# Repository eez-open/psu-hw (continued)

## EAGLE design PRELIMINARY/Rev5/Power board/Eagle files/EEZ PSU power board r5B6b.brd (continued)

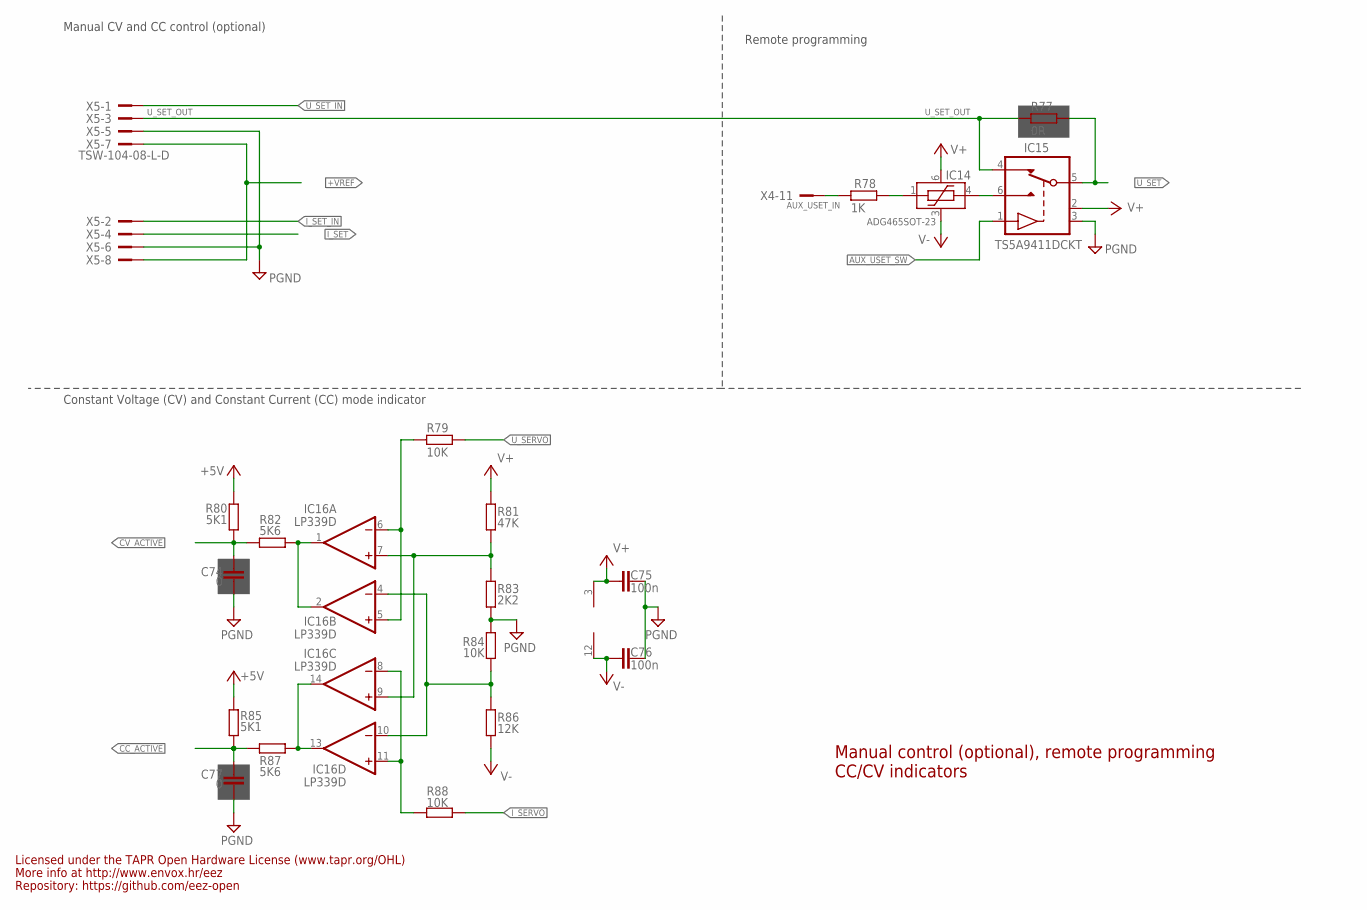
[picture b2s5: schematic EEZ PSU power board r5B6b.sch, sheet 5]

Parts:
C74, C77: 0; C0603
C75, C76: 100n; C0603
IC14: ADG465SOT-23; SOT95P280X145-6N
IC15: TS5A9411DCKT; SOT65P210X110-6N
IC16: LP339D; SOIC127P600X175-14N
R77: 0R; R0805
R78: 1K; R0805
R79, R84, R88: 10K; R0805
R80, R85: 5K1; R0805
R81: 47K; R0805
R82, R87: 5K6; R0805
R83: 2K2; R0805
R86: 12K; R0805
X4: SSW-113-02-T-D-RA; FARNELL 1805583
X5: TSW-104-08-L-D; TSW-104-02-S-D

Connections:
+5V: R80.2, R85.2; also elsewhere on the board
+VREF: X5.7, X5.8; also elsewhere on the board
AUX_USET_IN: R78.2, X4.11
AUX_USET_SW: IC15.1 (IN); also elsewhere on the board
CC_ACTIVE: C77.1, R85.1, R87.2; also elsewhere on the board
CV_ACTIVE: C74.1, R80.1, R82.2; also elsewhere on the board
GND: C74.2, C75.1, C76.1, C77.2, IC15.3 (GND), R83.1, R84.2, X5.5, X5.6; also elsewhere on the board
I_SERVO: R88.1; also elsewhere on the board
I_SET: X5.4; also elsewhere on the board
I_SET_IN: X5.2; also elsewhere on the board
unnamed: IC14.4 (VS), IC15.6 (S1)
unnamed: IC14.1 (VD), R78.1
unnamed: IC16.1 (OUT), IC16.2 (OUT), R82.1
unnamed: IC16.13 (OUT), IC16.14 (OUT), R87.1
unnamed: IC16.5 (+IN), IC16.6 (-IN), R79.2
unnamed: IC16.8 (-IN), IC16.11 (+IN), R88.2
unnamed: IC16.7 (+IN), IC16.9 (+IN), R81.1, R83.2
unnamed: IC16.4 (-IN), IC16.10 (-IN), R84.1, R86.2
U_SERVO: R79.1; also elsewhere on the board
U_SET: IC15.5 (D), R77.1; also elsewhere on the board
U_SET_IN: X5.1; also elsewhere on the board
U_SET_OUT: IC15.4 (S2), R77.2, X5.3
V+: C75.2, IC14.6 (VDD), IC15.2 (VDD), IC16.3 (V+), R81.2; also elsewhere on the board
V-: C76.2, IC14.3 (VSS), IC16.12 (GND), R86.1; also elsewhere on the board

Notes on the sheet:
Constant Voltage (CV) and Constant Current (CC) mode indicator
Manual CV and CC control (optional)
CC/CV indicators
Licensed under the TAPR Open Hardware License (www.tapr.org/OHL)
Repository: https://github.com/eez-open
More info at http://www.envox.hr/eez
Manual control (optional), remote programming
Remote programming

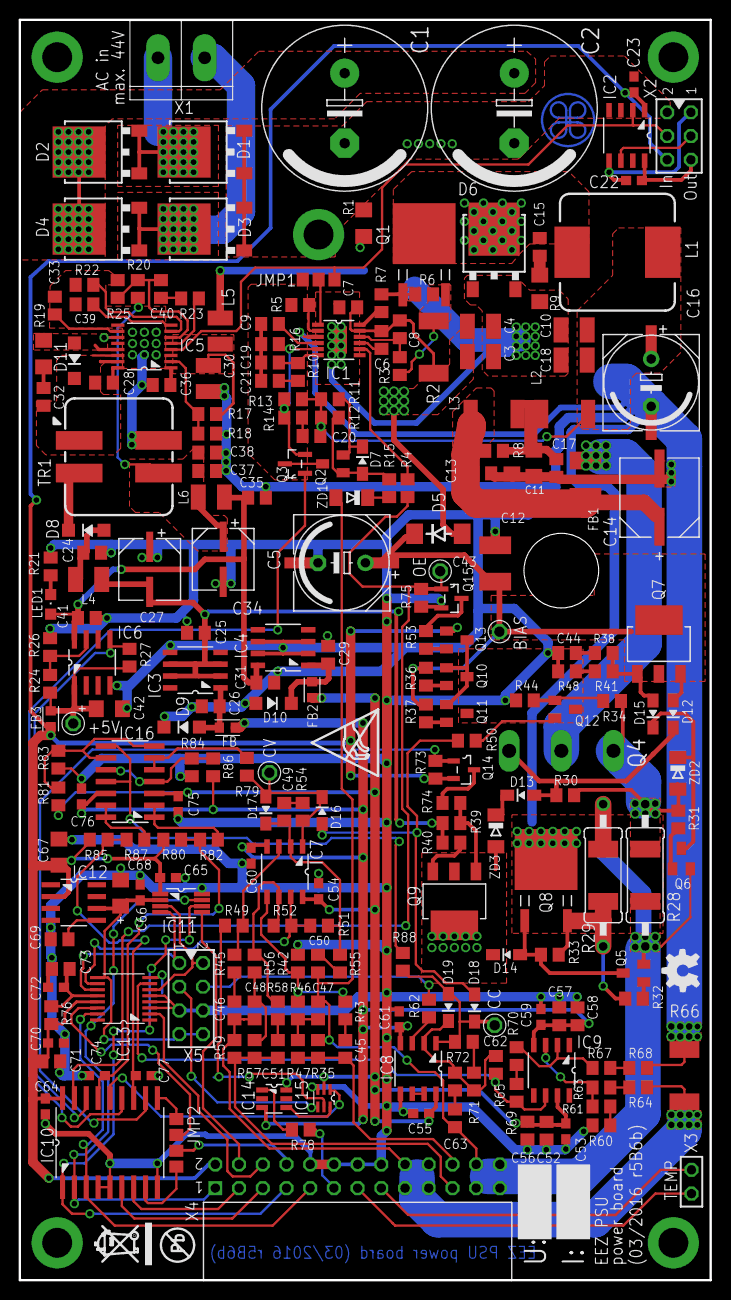
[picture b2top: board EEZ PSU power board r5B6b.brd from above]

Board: 3 copper layers, 74.0 x 135.0 mm, 248 parts (1 on the bottom side), 151 nets.

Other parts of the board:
EEZ_SIGNATURE: SIGNATURESMALL; SIGNATURE_5MM
U$2: RECYCLE_BIN1/8
U$3: PB_SMALL
U$4: ESD_SYMBOL
